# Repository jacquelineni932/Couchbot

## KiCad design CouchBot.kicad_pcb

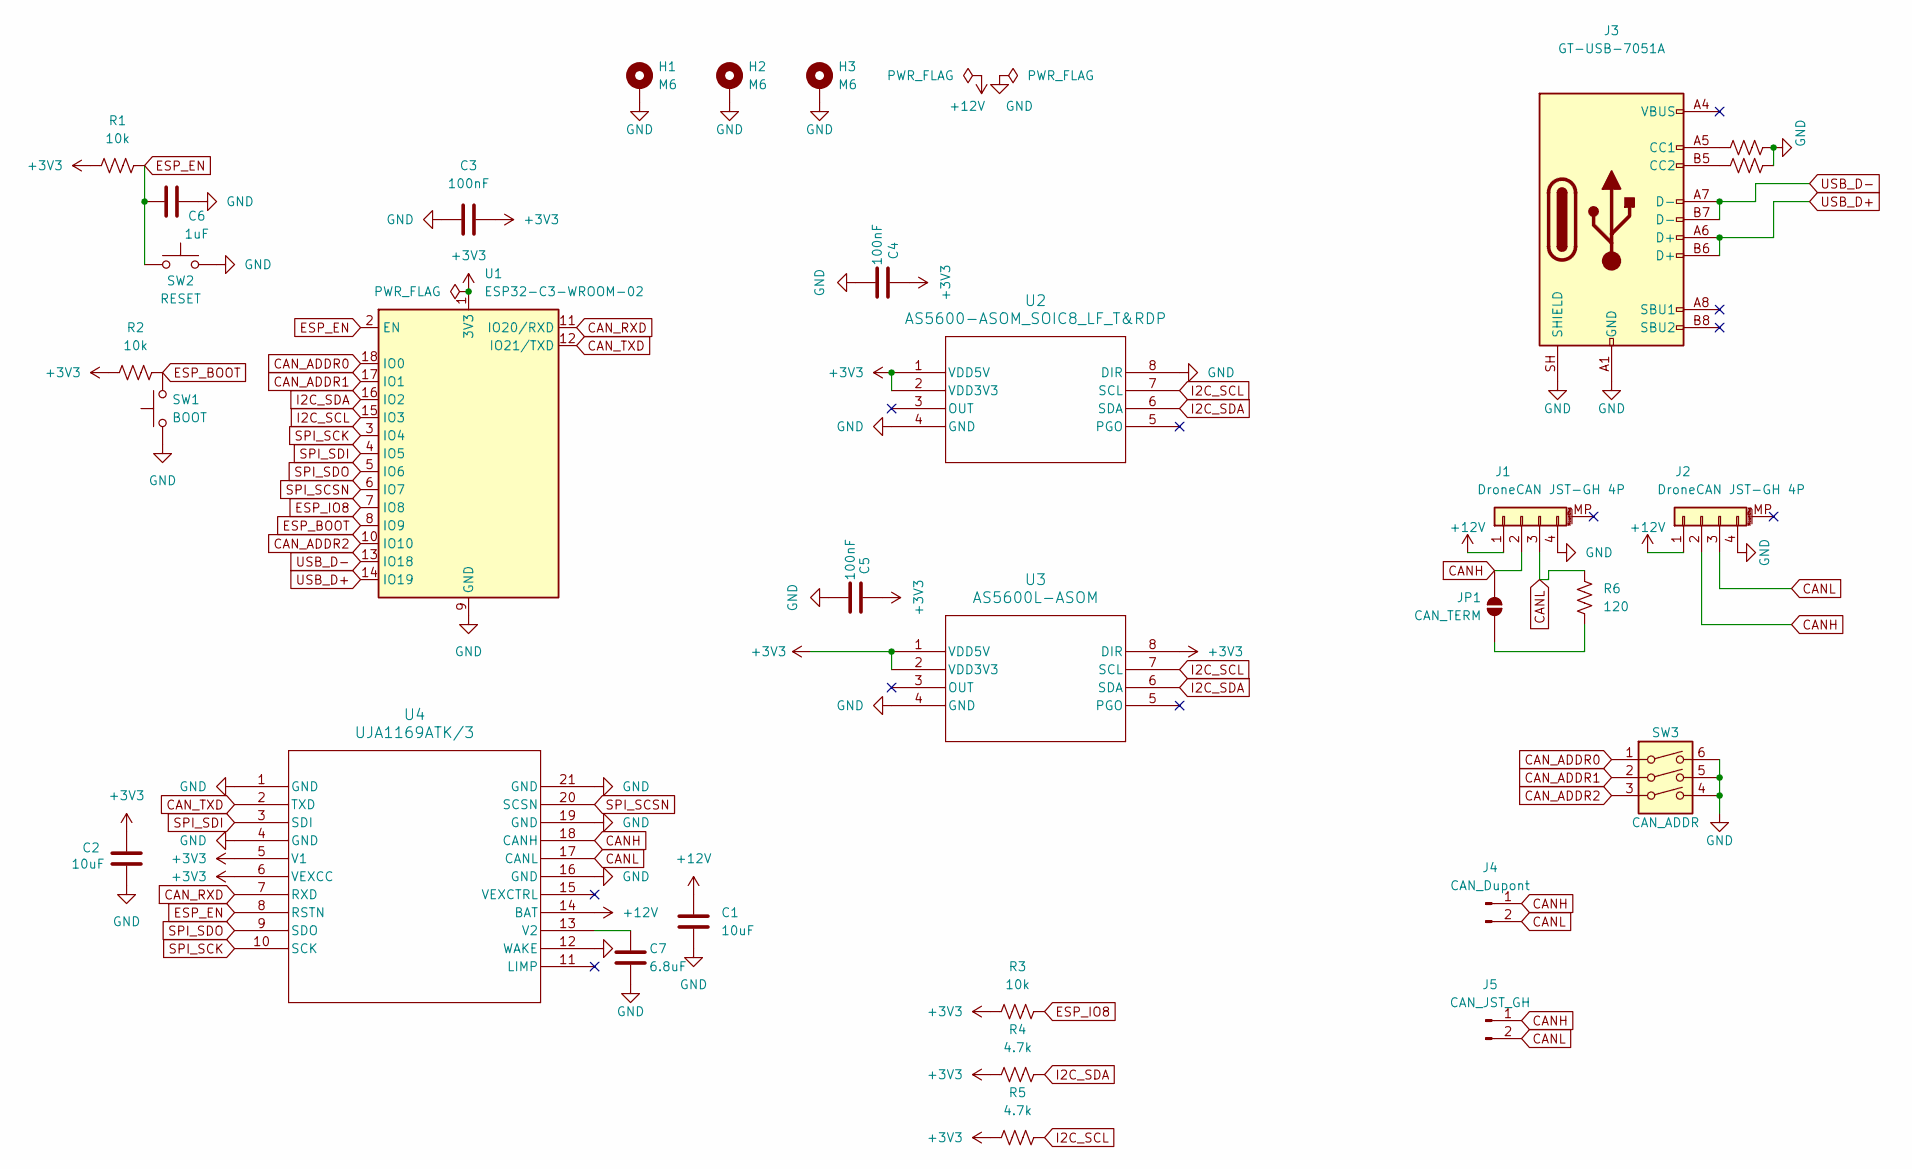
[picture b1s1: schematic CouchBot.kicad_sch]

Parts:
C1, C2: 10uF; C_0603_1608Metric
C3, C4, C5: 100nF; C_0603_1608Metric
C6: 1uF; C_0603_1608Metric
C7: 6.8uF; C_0603_1608Metric
H1, H2, H3: M6; MountingHole_6.4mm_M6_Pad_Via
J1, J2: DroneCAN JST-GH 4P; JST_GH_SM04B-GHS-TB_1x04-1MP_P1.25mm_Horizontal
J3: GT-USB-7051A; USB_C_Receptacle_G-Switch_GT-USB-7051x
J4: CAN_Dupont; PinHeader_1x02_P2.54mm_Vertical
J5: CAN_JST_GH; JST_GH_BM02B-GHS-TBT_1x02-1MP_P1.25mm_Vertical
JP1: CAN_TERM; SolderJumper-2_P1.3mm_Open_RoundedPad1.0x1.5mm
R1, R2, R3: 10k; R_0603_1608Metric
R4, R5: 4.7k; R_0603_1608Metric
R6: 120; R_0603_1608Metric
R7, R8: 5.1k; R_0603_1608Metric
SW1: BOOT; SW_SPST_TL3342
SW2: RESET; SW_SPST_TL3342
SW3: CAN_ADDR; SW_DIP_SPSTx03_Slide_9.78x9.8mm_W8.61mm_P2.54mm
U1: ESP32-C3-WROOM-02
U2: AS5600-ASOM_SOIC8_LF_T&RDP; SOIC-8_3.9x4.9mm_P1.27mm
U3: AS5600L-ASOM; SOIC-8_3.9x4.9mm_P1.27mm
U4: UJA1169ATK/3; U_HVSON20_NXP

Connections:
+3V3: C2.1, C3.1, C4.1, C5.1, R1.1, R2.1, R3.1, R4.1, R5.1, U1.1 (3V3), U2.1 (VDD5V), U2.2 (VDD3V3), U3.1 (VDD5V), U3.2 (VDD3V3), U3.8 (DIR), U4.5 (V1), U4.6 (VEXCC)
+12V: C1.1, J1.1, J2.1, U4.14 (BAT)
CANH: J1.2, J2.2, J4.1, J5.1, JP1.2 (B), U4.18 (CANH)
CANL: J1.3, J2.3, J4.2, J5.2, R6.1, U4.17 (CANL)
CAN_ADDR0: SW3.1, U1.18 (IO0)
CAN_ADDR1: SW3.2, U1.17 (IO1)
CAN_ADDR2: SW3.3, U1.10 (IO10)
CAN_RXD: U1.11 (IO20/RXD), U4.7 (RXD)
CAN_TXD: U1.12 (IO21/TXD), U4.2 (TXD)
ESP_BOOT: R2.2, SW1.2, U1.8 (IO9)
ESP_EN: C6.1, R1.2, SW2.1, U1.2 (EN), U4.8 (RSTN)
ESP_IO8: R3.2, U1.7 (IO8)
GND: C1.2, C2.2, C3.2, C4.2, C5.2, C6.2, C7.2, H1.1 (1_1), H2.1 (1_1), H3.1 (1_1), J1.4, J2.4, J3.A1 (GND), J3.A12 (GND), J3.B1 (GND), J3.B12 (GND), J3.SH (SHIELD), R7.2, R8.2, SW1.1, SW2.2, SW3.4, SW3.5, SW3.6, U1.9 (GND), U1.19 (GND), U2.4 (GND), U2.8 (DIR), U3.4 (GND), U4.1 (GND), U4.4 (GND), U4.12 (WAKE), U4.16 (GND), U4.19 (GND), U4.21 (GND)
I2C_SCL: R5.2, U1.15 (IO3), U2.7 (SCL), U3.7 (SCL)
I2C_SDA: R4.2, U1.16 (IO2), U2.6 (SDA), U3.6 (SDA)
unnamed: J3.A5 (CC1), R7.1
unnamed: J3.B5 (CC2), R8.1
unnamed: JP1.1 (A), R6.2
unnamed: C7.1, U4.13 (V2)
SPI_SCK: U1.3 (IO4), U4.10 (SCK)
SPI_SCSN: U1.6 (IO7), U4.20 (SCSN)
SPI_SDI: U1.4 (IO5), U4.3 (SDI)
SPI_SDO: U1.5 (IO6), U4.9 (SDO)
USB_D+: J3.A6 (D+), J3.B6 (D+), U1.14 (IO19)
USB_D-: J3.A7 (D-), J3.B7 (D-), U1.13 (IO18)

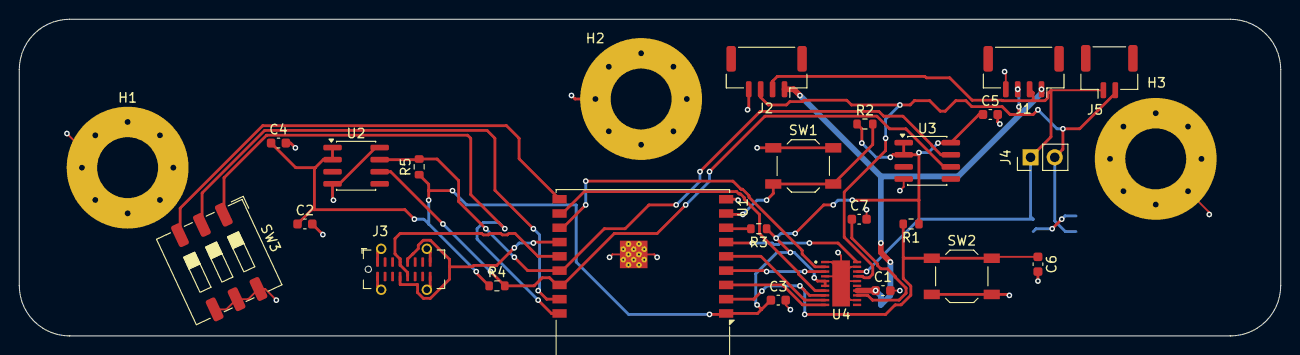
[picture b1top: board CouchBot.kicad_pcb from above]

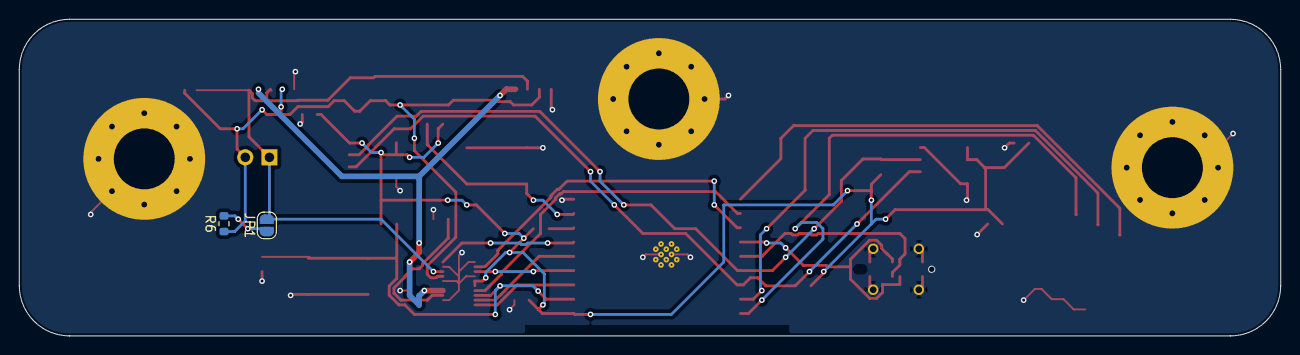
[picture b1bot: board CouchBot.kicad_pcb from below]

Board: 2 copper layers, 132.5 x 33.3 mm, 29 parts (2 on the bottom side), 23 nets.
